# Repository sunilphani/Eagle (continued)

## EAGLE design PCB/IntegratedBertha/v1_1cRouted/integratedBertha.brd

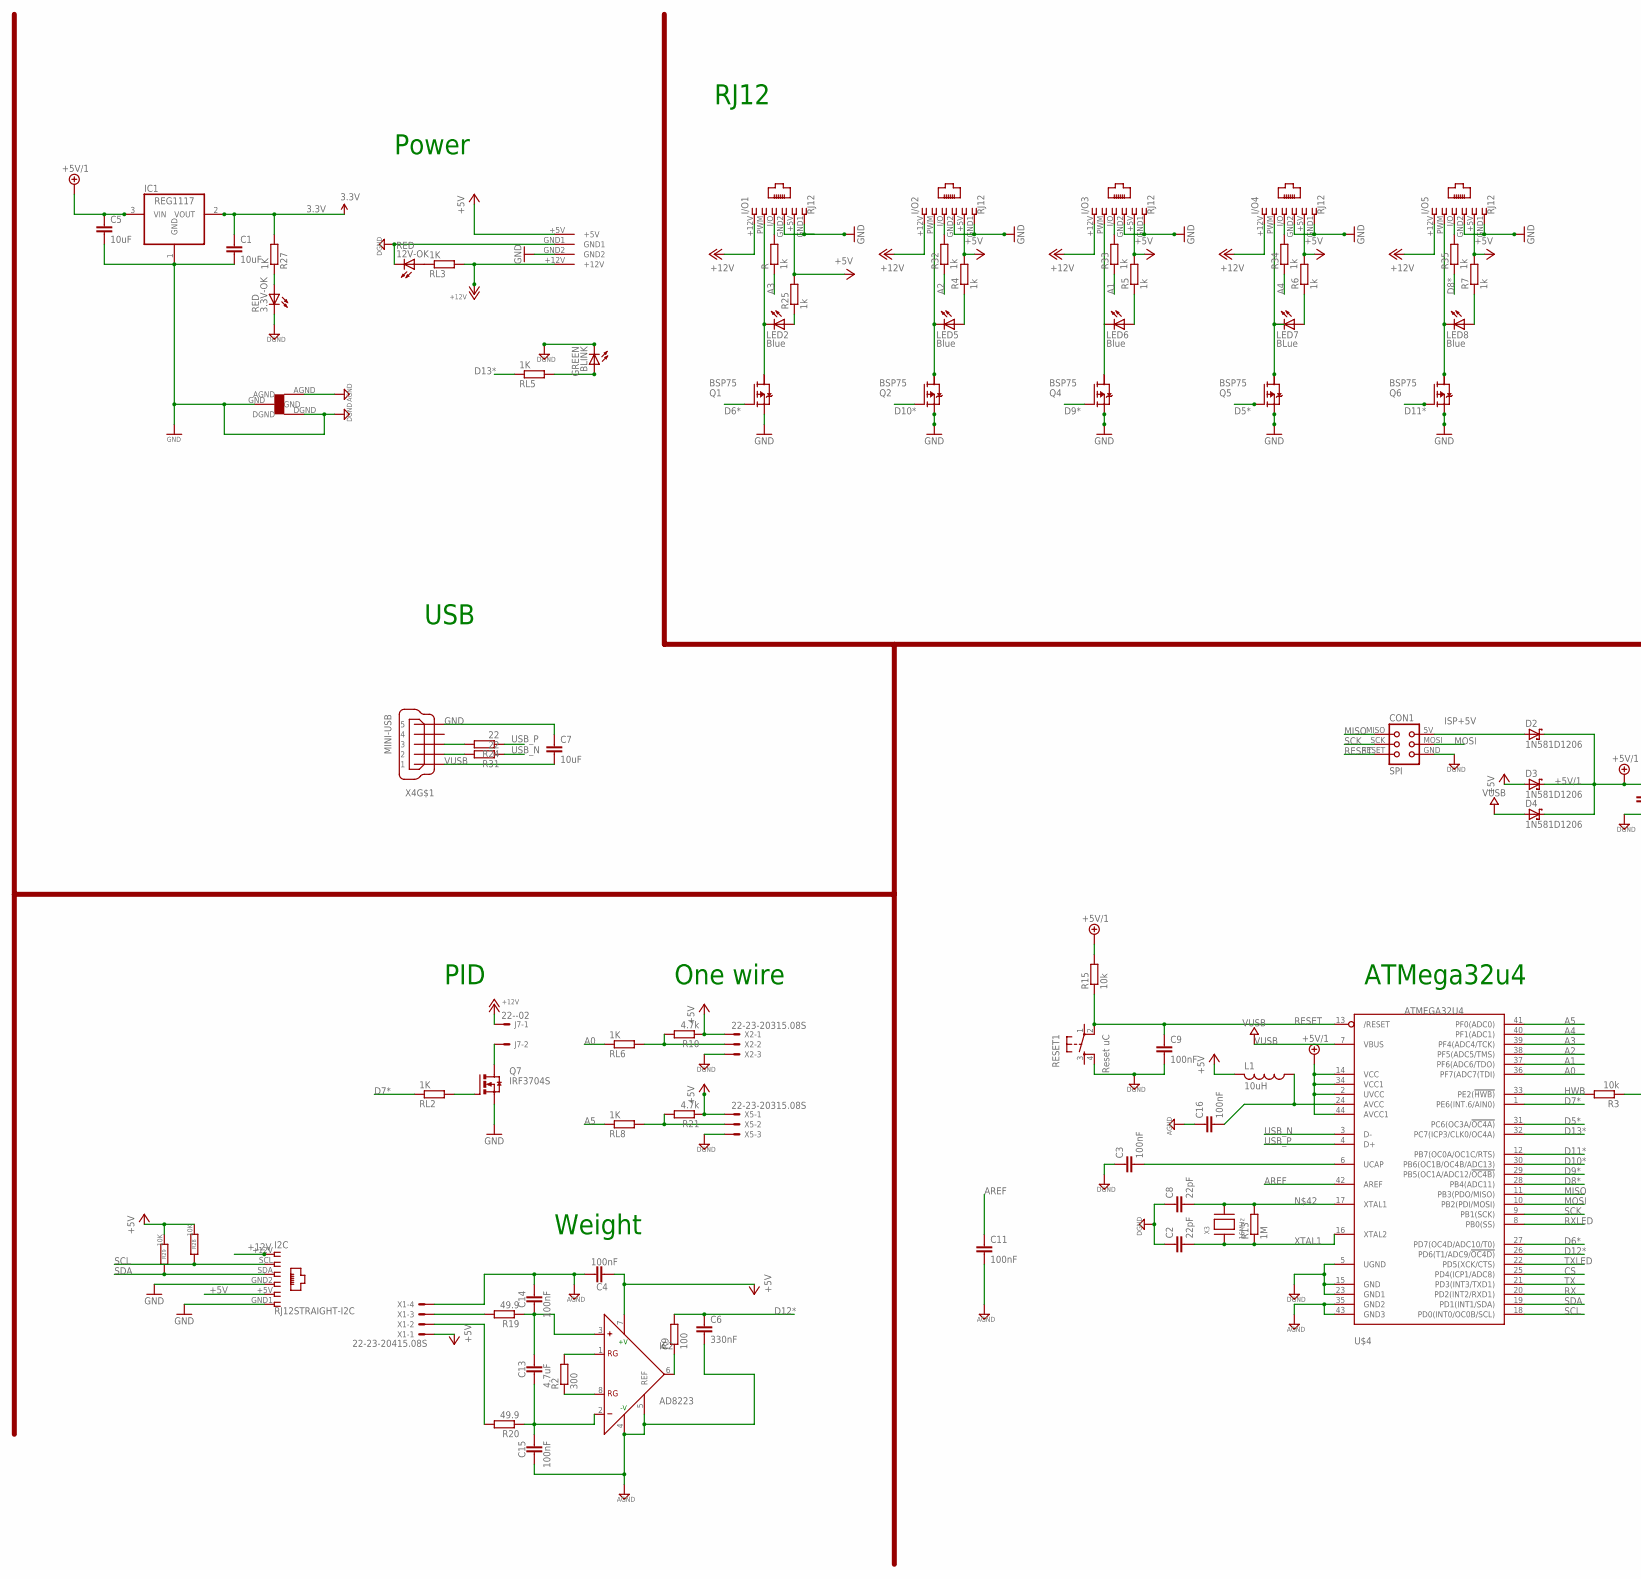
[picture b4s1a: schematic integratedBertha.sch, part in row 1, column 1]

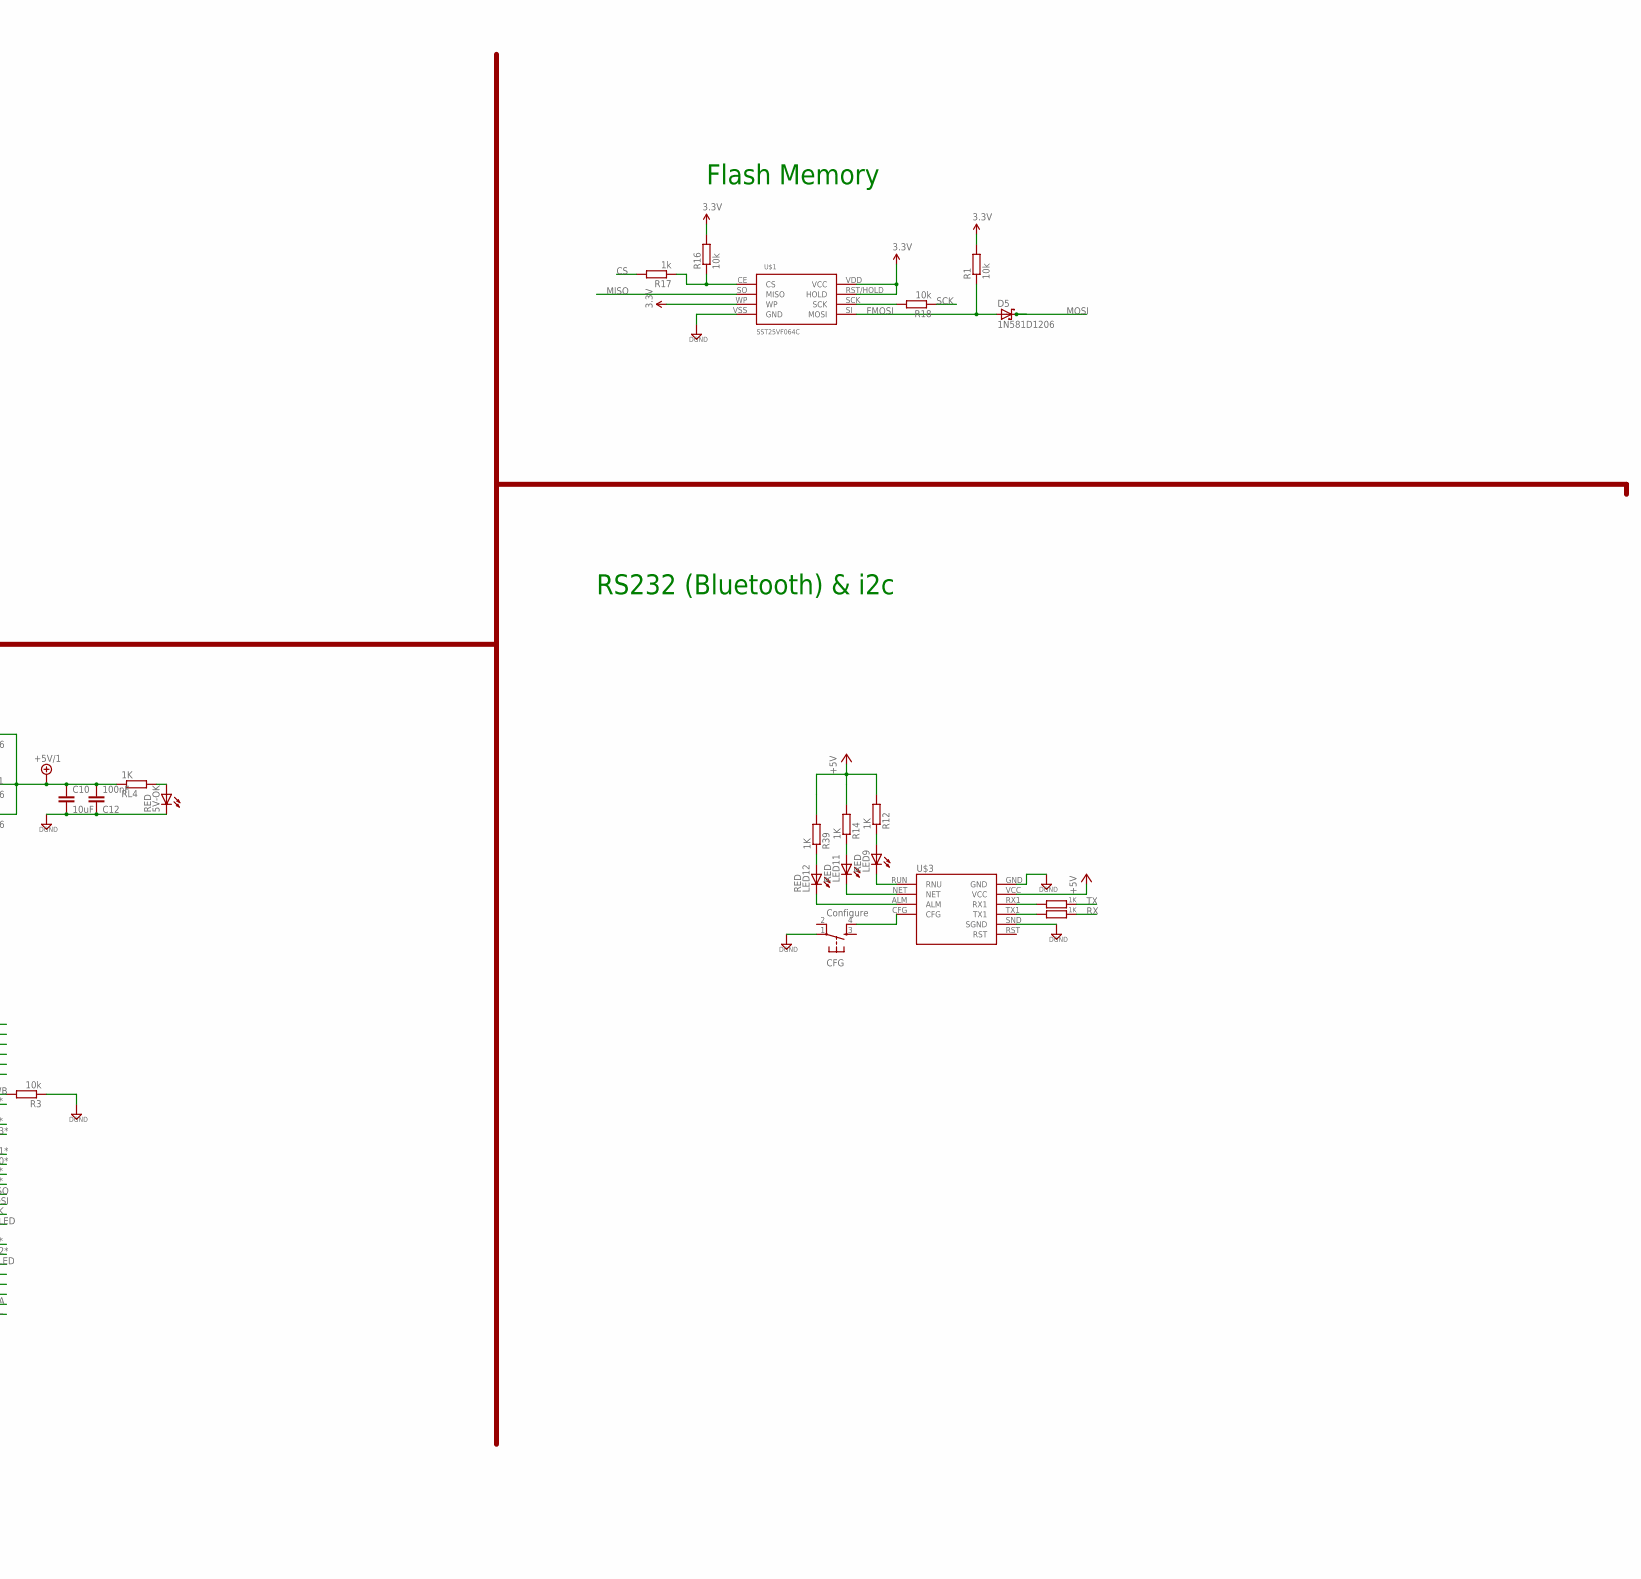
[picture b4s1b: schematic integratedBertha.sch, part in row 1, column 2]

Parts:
3.3V-OK, 5V-OK, 12V-OK: RED; CHIPLED_1206
BLINK: GREEN; CHIPLED_1206
C1, C5, C7, C10: 10uF; C1206
C2, C8: 22pF; C1206
C3, C4, C9, C11, C12, C14, C15, C16: 100nF; C1206
C6: 330nF; C1206
C13: 4.7uF; C1206
CFG: Configure; TACTILE_SWITCH_SMD
CON1: SPI; TC2030-MCP-NL
D2, D3, D4, D5: 1N581D1206; LED-1206
I2C: RJ12STRAIGHT-I2C; RJ12-STRAIGHT-I2C
I/O1, I/O2, I/O3, I/O4, I/O5: RJ12; RJ12-STRAIGHT
IC1: REG1117; SOT223
IC2: AD8223; SO8
J7: 22--02; 2-PIN-5.08S
L1: 10uH; L2012C
LED2, LED5, LED6, LED8: Blue; CHIPLED_1206
LED7: BLue; CHIPLED_1206
LED9, LED11, LED12: RED; CHIPLED_1206
Q1, Q2, Q4, Q5, Q6: BSP75; PG-SOT-223
Q7: IRF3704S; D2PACK
R, R4, R5, R6, R7, R17, R25, R32, R33, R34, R35: 1k; R0805
R1, R16, R18: 10k; R0805
R2: 300; R1206
R3, R15: 10k; M0805
R8, R11, R12, R14, R27, R39: 1K; R0805
R9: 100; R1206
R10, R21: 4.7k; R1206
R13: 1M; R1206
R19, R20: 49.9; R1206
R24, R31: 22; M1206
R28, R29: 10K; M0805
RESET1: Reset uC; TACTILE_SWITCH_SMD
RL2, RL3, RL4, RL5, RL6, RL8: 1K; R0805
U$1: SST25VF064C; SOIC_8-LEAD
U$2: STARGND; STAR
U$3: SZ05-ZIGBEE; SZ05-ZIGBEE4
U$4: ATMEGA32U4; TQFP44
U$6: KPJX-4S-S
X1: 22-23-20415.08S; 4-PIN-5.08S
X2, X5: 22-23-20315.08S; 3-PIN-5.08S
X3: 16MHz; NX6035
X4: MINI-USB; 32005-201

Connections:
3.3V: C1.1, IC1.2 (VOUT), R1.2, R16.2, R27.2, U$1.RST/HOLD (HOLD), U$1.VDD (VCC), U$1.WP
+5V: C4.2, D3.A, I2C.+5V (5), I/O1.+5V (5), I/O2.+5V (5), I/O3.+5V (5), I/O4.+5V (5), I/O5.+5V (5), IC2.7 (+V), L1.2, R4.2, R5.2, R6.2, R7.2, R10.1, R12.2, R14.2, R21.1, R25.2, R28.1, R29.1, R39.2, U$3.VCC, U$6.+5V, X1.1, X2.1, X5.1
+5V/1: C5.1, C10.1, C12.2, D2.C, D3.C, D4.C, IC1.3 (VIN), R15.2, RL4.1, U$4.2 (UVCC), U$4.14 (VCC), U$4.34 (VCC1), U$4.44 (AVCC1)
+12V: I2C.+12V (1), I/O1.+12V (1), I/O2.+12V (1), I/O3.+12V (1), I/O4.+12V (1), I/O5.+12V (1), J7.1, RL3.2, U$6.+12V
A0: RL6.1, U$4.36 (PF7(ADC7(TDI))
A1: R33.1, U$4.37 (PF6(ADC6/TDO))
A2: R32.1, U$4.38 (PF5(ADC5/TMS))
A3: R.1, U$4.39 (PF4(ADC4/TCK))
A4: R34.1, U$4.40 (PF1(ADC1))
A5: RL8.1, U$4.41 (PF0(ADC0))
AGND: C4.1, C6.2, C11.2, C14.1, C15.2, C16.1, IC2.4 (-V), IC2.5 (REF), U$2.AGND, U$4.35 (GND2), U$4.43 (GND3), X1.4
AREF: C11.1, U$4.42 (AREF)
CS: R17.2, U$4.25 (PD4(ICP1/ADC8))
D5*: Q5.1 (G), U$4.31 (PC6(OC3A/!OC4A))
D6*: Q1.1 (G), U$4.27 (PD7(OC4D/ADC10/T0))
D7*: RL2.1, U$4.1 (PE6(INT.6/AIN0))
D8*: R35.1, U$4.28 (PB4(ADC11))
D9*: Q4.1 (G), U$4.29 (PB5(OC1A/ADC12/!OC4B))
D10*: Q2.1 (G), U$4.30 (PB6(OC1B/OC4B/ADC13))
D11*: Q6.1 (G), U$4.12 (PB7(OC0A/OC1C/RTS))
D12*: C6.1, R9.2, U$4.26 (PD6(T1/ADC9/!OC4D))
D13*: RL5.1, U$4.32 (PC7(ICP3/CLK0/OC4A))
DIFF+: C13.1, C14.2, IC2.3 (+), R19.1
DIFF-: C13.2, C15.1, IC2.2 (-), R20.1
FMOSI: D5.A, R1.1, U$1.SI (MOSI)
GND: 3.3V-OK.C, 5V-OK.C, 12V-OK.C, BLINK.C, C1.2, C2.1, C3.1, C5.2, C7.1, C8.1, C9.2, C10.2, C12.1, CFG.1, CON1.GND, I2C.GND1 (6), I2C.GND2 (4), I/O1.GND1 (6), I/O1.GND2 (4), I/O2.GND1 (6), I/O2.GND2 (4), I/O3.GND1 (6), I/O3.GND2 (4), I/O4.GND1 (6), I/O4.GND2 (4), I/O5.GND1 (6), I/O5.GND2 (4), IC1.1 (GND), Q1.3 (S), Q2.3 (S), Q4.3 (S), Q5.3 (S), Q6.3 (S), Q7.3 (S), R3.1, RESET1.4, U$1.VSS (GND), U$2.DGND, U$2.GND, U$3.GND, U$3.SND (SGND), U$4.5 (UGND), U$4.15 (GND), U$4.23 (GND1), U$6.GND1, U$6.GND2, X2.3, X4.5, X5.3
GND1: LED9.C, U$3.RUN (RNU)
GND2: LED11.C, U$3.NET
GND3: LED12.C, U$3.ALM
HWB: R3.2, U$4.33 (PE2(!HWB))
ISP+5V: CON1.5V (VCC), D2.A
MISO: CON1.MISO, U$1.SO (MISO), U$4.11 (PB3(PDO/MISO))
MOSI: CON1.MOSI, D5.C, U$4.10 (PB2(PDI/MOSI))
unnamed: I/O3.PWM (2), LED6.C, Q4.2 (D)
unnamed: I/O2.I/O (3), R32.2
unnamed: BLINK.A, RL5.2
unnamed: LED5.A, R4.1
unnamed: I/O4.PWM (2), LED7.C, Q5.2 (D)
unnamed: Q7.1 (G), RL2.2
unnamed: I/O3.I/O (3), R33.2
unnamed: R21.2, RL8.2, X5.2
unnamed: R16.1, R17.1, U$1.CE (CS)
unnamed: R11.2, U$3.RX1
unnamed: 5V-OK.A, RL4.2
unnamed: IC2.1 (RG), R2.2
unnamed: C16.2, L1.1, U$4.24 (AVCC)
unnamed: IC2.8 (RG), R2.1
unnamed: C3.2, U$4.6 (UCAP)
unnamed: LED2.A, R25.1
unnamed: I/O1.I/O (3), R.2
unnamed: I/O5.PWM (2), LED8.C, Q6.2 (D)
unnamed: 3.3V-OK.A, R27.1
unnamed: R10.2, RL6.2, X2.2
unnamed: LED6.A, R5.1
unnamed: R18.2, U$1.SCK
unnamed: R8.2, U$3.TX1
unnamed: LED9.A, R12.1
unnamed: LED11.A, R14.1
unnamed: LED12.A, R39.1
unnamed: I/O2.PWM (2), LED5.C, Q2.2 (D)
unnamed: I/O4.I/O (3), R34.2
unnamed: LED7.A, R6.1
unnamed: R20.2, X1.2
unnamed: I/O5.I/O (3), R35.2
unnamed: LED8.A, R7.1
unnamed: I/O1.PWM (2), LED2.C, Q1.2 (D)
unnamed: CFG.4, U$3.CFG
unnamed: J7.2, Q7.2 (D)
unnamed: R19.2, X1.3
unnamed: IC2.6 (OUT), R9.1
unnamed: C8.2, R13.2, U$4.17 (XTAL1), X3.P$2
unnamed: 12V-OK.A, RL3.1
RESET: C9.1, CON1.RESET, R15.1, RESET1.2, U$4.13 (/RESET)
RX: R8.1, U$4.20 (PD2(INT2/RXD1))
RXLED: U$4.8 (PB0(SS))
SCK: CON1.SCK, R18.1, U$4.9 (PB1(SCK))
SCL: I2C.SCL (2), R28.2, U$4.18 (PD0(INT0/OC0B/SCL))
SDA: I2C.SDA (3), R29.2, U$4.19 (PD1(INT1/SDA))
TX: R11.1, U$4.21 (PD3(INT3/TXD1))
TXLED: U$4.22 (PD5(XCK/CTS))
USBC_N: R31.2, X4.2
USBC_P: R24.2, X4.3
USB_N: R31.1, U$4.3 (D-)
USB_P: R24.1, U$4.4 (D+)
VUSB: C7.2, D4.A, U$4.7 (VBUS), X4.1
XTAL1: C2.2, R13.1, U$4.16 (XTAL2), X3.P$1

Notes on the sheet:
Flash Memory
RJ12
ATMega32u4
USB
Power
RS232 (Bluetooth) & i2c
PID
One wire
Weight

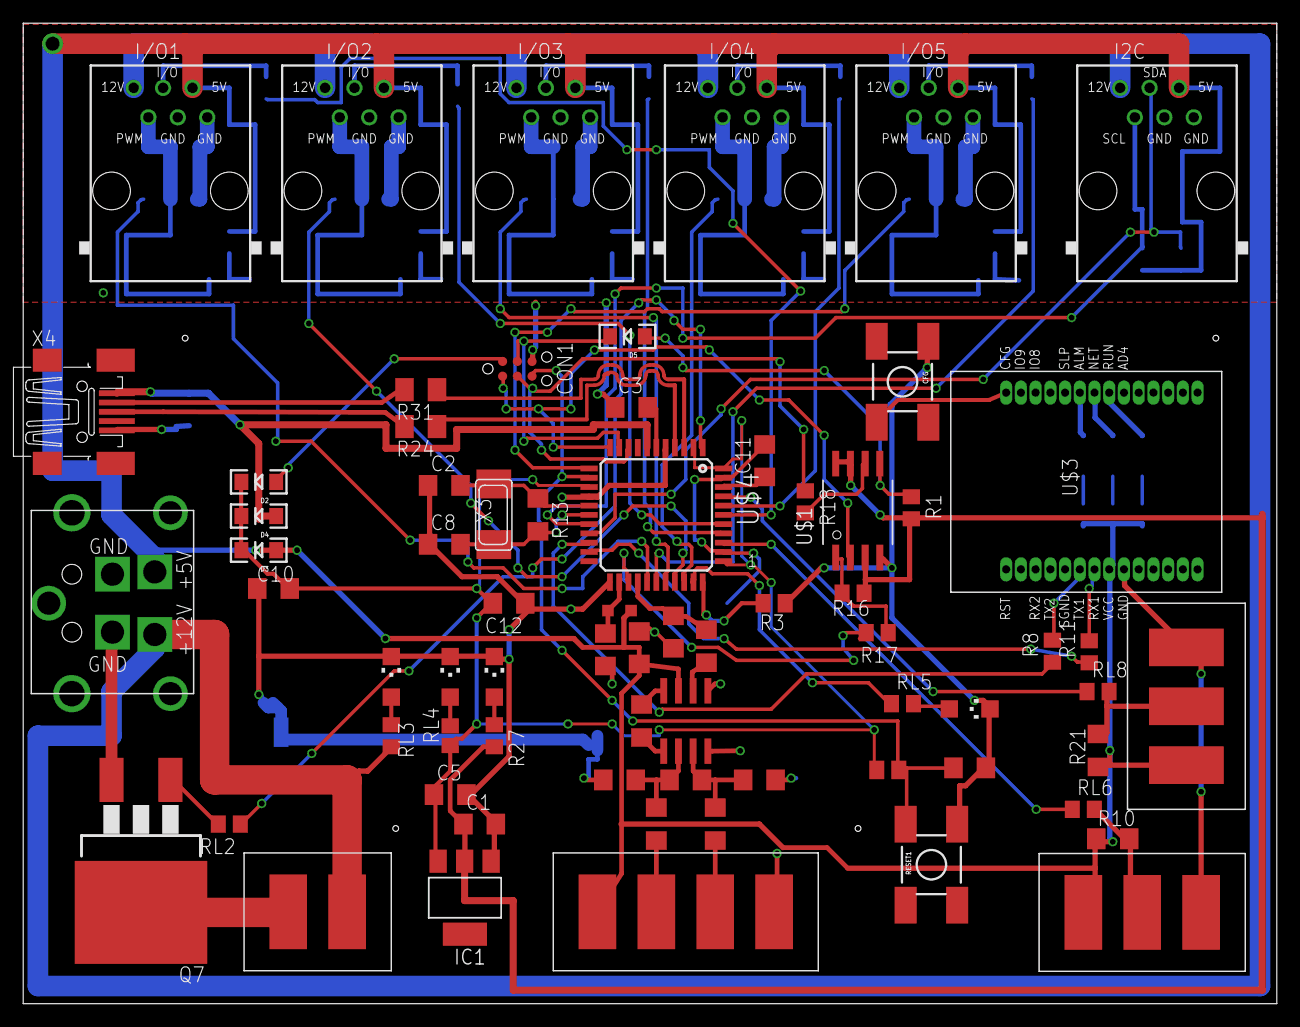
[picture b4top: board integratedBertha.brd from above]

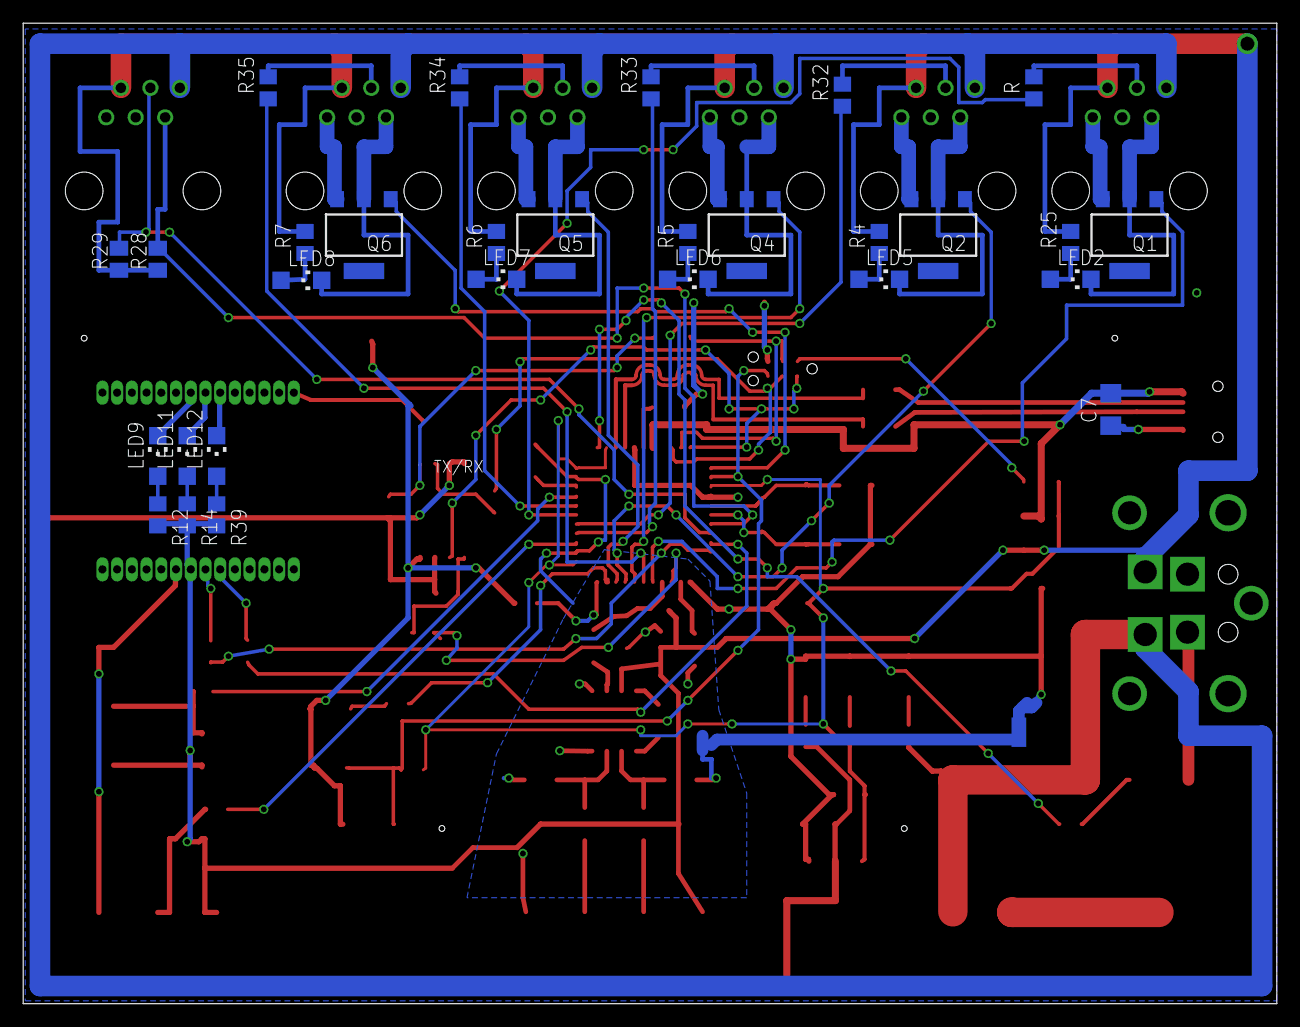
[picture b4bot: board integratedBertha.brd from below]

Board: 4 copper layers, 108.1 x 84.6 mm, 100 parts (30 on the bottom side), 84 nets.

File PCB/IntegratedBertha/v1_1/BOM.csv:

"Qty";"Value";"Device";"Package";"Parts";"Description";"";
"1";"100";"R-EU_R1206";"R1206";"R9";"RESISTOR, European symbol";"";
"7";"100nF";"C-EUC1206";"C1206";"C3, C4, C9, C11, C12, C14, C15";"CAPACITOR, European symbol";"";
"1";"100uF";"C-EUC1206";"C1206";"C16";"CAPACITOR, European symbol";"";
"2";"10K";"R-EU_M0805";"M0805";"R28, R29";"RESISTOR, European symbol";"";
"2";"10k";"R-EU_M0805";"M0805";"R3, R15";"RESISTOR, European symbol";"";
"3";"10k";"R-EU_R0805";"R0805";"R1, R16, R18";"RESISTOR, European symbol";"";
"4";"10uF";"C-EUC1206";"C1206";"C1, C5, C7, C10";"CAPACITOR, European symbol";"";
"1";"10uH";"L-USL2012C";"L2012C";"L1";"INDUCTOR, American symbol";"";
"1";"16MHz";"XTALNX6035";"NX6035";"X3";"Low cost SMT crystals, no capacitors included";"";
"12";"1K";"R-EU_R0805";"R0805";"R8, R11, R12, R14, R27, R39, RL2, RL3, RL4, RL5, RL6, RL8";"RESISTOR, European symbol";"";
"1";"1M";"R-EU_R1206";"R1206";"R13";"RESISTOR, European symbol";"";
"4";"1N581D1206";"1N581D1206";"LED-1206";"D2, D3, D4, D5";"1.0A SCHOTTKY BARRIER RECTIFIER";"";
"11";"1k";"R-EU_R0805";"R0805";"R, R4, R5, R6, R7, R17, R25, R32, R33, R34, R35";"RESISTOR, European symbol";"";
"2";"22";"R-EU_M1206";"M1206";"R24, R31";"RESISTOR, European symbol";"";
"1";"22--02";"22--02";"2-PIN-5.08S";"J7";"CONNECTOR";"";
"2";"22-23-20315.08S";"22-23-20315.08S";"3-PIN-5.08S";"X2, X5";".100" (2.54mm) Center Header - 3 Pin";"";
"1";"22-23-20415.08S";"22-23-20415.08S";"4-PIN-5.08S";"X1";".100" (2.54mm) Center Header - 4 Pin";"";
"2";"22pF";"C-EUC1206";"C1206";"C2, C8";"CAPACITOR, European symbol";"";
"1";"300";"R-EU_R1206";"R1206";"R2";"RESISTOR, European symbol";"";
"1";"330nF";"C-EUC1206";"C1206";"C6";"CAPACITOR, European symbol";"";
"2";"4.7k";"R-EU_R1206";"R1206";"R10, R21";"RESISTOR, European symbol";"";
"1";"4.7uF";"C-EUC1206";"C1206";"C13";"CAPACITOR, European symbol";"";
"2";"49.9";"R-EU_R1206";"R1206";"R19, R20";"RESISTOR, European symbol";"";
"1";"AD8223";"AD620R";"SO8";"IC2";"Low Cost, Low Power, Instrumentation Amplifier";"";
"1";"ATMEGA32U4";"ATMEGA32U4-AU";"TQFP44";"U$4";"http://www.ladyada.net/library/eagle";"";
"1";"BLue";"LEDCHIPLED_1206";"CHIPLED_1206";"LED7";"LED";"";
"5";"BSP75";"BSP613P";"PG-SOT-223";"Q1, Q2, Q4, Q5, Q6";"SIPMOS (R) Small-Signal-Transistor P-Channel (2 Drain)";"";
"4";"Blue";"LEDCHIPLED_1206";"CHIPLED_1206";"LED2, LED5, LED6, LED8";"LED";"";
"1";"Configure";"TAC_SWITCHSMD";"TACTILE_SWITCH_SMD";"CFG";"Momentary Switch";"";
"1";"GREEN";"LEDCHIPLED_1206";"CHIPLED_1206";"BLINK";"LED";"";
"1";"IRF3704S";"IRF3704S";"D2PACK";"Q7";"SMPS MOSFET";"";
"1";"KPJX-4S-S";"KPJX-4S-S";"KPJX-4S-S";"U$6";"";"";
"1";"MINI-USB";"MINI-USB-SCHIELD-32005-201";"32005-201";"X4";"MINI USB-B Conector";"";
"6";"RED";"LEDCHIPLED_1206";"CHIPLED_1206";"3.3V-OK, 5V-OK, 12V-OK, LED9, LED11, LED12";"LED";"";
"1";"REG1117";"REG1117";"SOT223";"IC1";"800mA and 1A Low Dropout (LDO) Positive Regulator";"";
"5";"RJ12";"RJ12STRAIGHT";"RJ12-STRAIGHT";"I/O1, I/O2, I/O3, I/O4, I/O5";"CORCOM Modular RJ Jacks No Shield";"";
"1";"RJ12STRAIGHT-I2C";"RJ12STRAIGHT-I2C";"RJ12-STRAIGHT-I2C";"I2C";"CORCOM Modular RJ Jacks No Shield";"";
"1";"Reset uC";"TAC_SWITCHSMD";"TACTILE_SWITCH_SMD";"RESET1";"Momentary Switch";"";
"1";"SPI";"TINYISPT";"TC2030-MCP-NL";"CON1";"CONNECTOR";"";
"1";"SST25VF064C";"SST25VF064C";"SOIC_8-LEAD";"U$1";"";"";
"1";"STARGND";"STARGND";"STAR";"U$2";"";"";
"1";"SZ05-ZIGBEE";"SZ05-ZIGBEETHROUGHHOLE";"SZ05-ZIGBEE4";"U$3";"";"";

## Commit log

2014-04-30 Eagle files
2014-05-01 Update eagle
2014-05-08 Update cards
2014-05-21 Update labels
2014-05-24 Update labels of sensor
2014-05-24 Update annotation
2014-06-11 First version of Valve Driver
2014-06-14 Create new verison
2014-06-14 Update annotations
2014-06-22 Update Board
2014-06-30 Solar Decathlon v1
2014-07-02 Update wiegand
2014-07-02 Add routing
2014-07-02 add cam layers
2014-07-02 Update board adding a LED
2014-07-03 New version based on BSP 75
2014-07-03 jul
    design
2014-07-07 Add relay card and integrated bioreactor
2014-07-08 Update integrated
2014-07-08 add 2 relay copy
2014-07-08 jul updates gerber for wiegand 1.1
2014-07-08 Add small connector
2014-07-10 Update anemometer
2014-07-11 Upate anemometer
2014-07-11 Autorouting completed, ground plane added on both sides
2014-07-16 Remove useless file
2014-07-16 added version 2 that was sent to factory
2014-07-22 Created version 4
2014-07-22 added ground plane. connected AD negative input in star configuration
2014-07-25 Added filter capacitances in version 1.1. not yet in v1.1b
2014-07-28 added RF filter capacitances. autorouter works still 100percent
2014-07-28 modified pin configuration to newest version as in googledocs
2014-07-29 resolved french accent problem with berta control card
2014-07-29 in v1.1b, made the USB traces have the same lenght
2014-07-29 added lpatiny.lbr and added throughhole footprint for small zigbee module. CHANGED DESIGN RULES (according to seeedstudios design rules)
2014-07-31 put all devices on one side on integrated bertha
2014-07-31 deleted some files
2014-08-01 routed anemometer and integrated bertha with ground planes and separate analog and digital ground. ready for fabrication
2014-08-01 integratedBertha v1.1: adjusted labels to good position. Anemometer: added ferrite bead for vcc decoupling and ground line.
2014-08-01 added relay card with jumpers. adjusted labels in anemometer
2014-08-01 Added door locking pcb with gerber files.
2014-08-01 created GERBER files for integratedBertha, anemometer, relay3, door locking pcb. Changed CAM processor file (corrected a bug in silk layer, added a job with univalle/EPFL logos on bottom side).
2014-08-04 Prototype with AT90usb controller
2014-08-04 changed some labels, corrected C16 value in bertha. created BOM
2014-08-04 also in v1_1b
2014-08-04 corrected errors in wiedgand
2014-08-05 Re-added mass line for security
2014-08-05 Error on local isolated mass corrected
2014-08-05 Corrected mass error (manual shunt to do on the previous board)
2014-08-06 created BOMS, deleted useless files
2014-08-06 deleted useless files
2014-08-07 removed tDocu and bDocu from silk layer
2014-08-07 included .TXT-file in gerber archive.
2014-08-13 door locking v1.2
2014-08-13 the scketch with the gerber
2014-08-14 Jumper for 12V, routed
2014-08-20 corrected silk layer in anemometer
2014-08-25 ph meter independant
2014-08-25 Modification SolarDecathlon, changed the format for Dallas in uSOP8, added
    new file: Libraries/lomasenlibraries (3).l#1
    new file: Libraries/lomasenlibraries (3).lbr
    new file: Libraries/mcp3424.lbr
    new file: PCB/SolarDecathlon/v1.1/REVISON_NOTE.txt
    new file: PCB/SolarDecathlon/v1.1/SOLAR_V1.1_GERBER.zip
    new file: PCB/SolarDecathlon/v1.1/SOLAR_V1.1_GERBER/v1.GBL
2014-08-26 created v5 anemometer with identic channels
2014-08-26 created gerber for anemo5
2014-08-26 adapted label positions in integrated bertha 1.1 and created new gerbers
2014-08-28 corrected boards to fulfill design rules of the factory in Bogota (drill size and copper spacing. small changes in solardecathlon (SPI pins and design rules changed for zigbee header pads
2014-08-31 Update bertha to last eagle
2014-10-16 changet to PNP darlington in unrouted anemometer file. should be rerouted if needed! (no changes in routed files...)
2014-11-03 Solar Decathlon V2 w/ current sense - panelized boards
2014-11-03 -cleaned local modif on v1.1
2014-11-12 corrected hacks for zigbee power supply on Solar pcb
2015-01-27 small test PCB for I2C sun sensors compatible with SolarDecathlon
2015-01-27 cleaned archives
2015-01-28 test PCB for sun sensors TSL and SI created
